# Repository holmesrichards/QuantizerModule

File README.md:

# QuantizerModule
Code and hardware for Kosmo/Eurorack quantizer module

This is a dual quantizer based on the [dac/ino](https://github.com/holmesrichards/dac_ino) board. As such it uses the dac\_ino library as well as the Quantizer library in this repository. 

Design is for Kosmo format module but the PCB and code would work equally well for a Eurorack version if the board were mounted perpendicular to the panel. It would just need a smaller front panel. Likewise with perpendicular mounting it could be a smaller single Kosmo quantizer.

## Front panel
On the front panel, for each quantizer section, are:

- CV1 and CV2 inputs
- Quantize gate input
- Trigger input
- CV output
- CV2 attenuator
- Quantize toggle switch
- Scale selection 12 position rotary switch
- Bank selection 6 position switch

## Use
The control voltage to be quantized is plugged into CV1. It should be in the range 0–5 volts, though voltages outside this range (within reason) shouldn't cause damage.

CV2 is an offset; it is added to the quantized CV1 to produce the output. It should also be in the range 0–5 volts. It can be attenuated with the knob. Normalled value is 5 volts before attenuation.

The Quantize switch can be used to disable quantization, in which case the output CV is just CV1 + CV2 (attenuated). If the Quantize switch is on and a gate source is plugged into the Quantize input, quantization is on only when the gate is on. If nothing is plugged in and the Quantize switch is on, quantization is on.

If nothing is plugged into the Trigger input, the input control voltages are sampled and the output control voltage is updated continually. If a trigger or gate source is plugged in, updating occurs only when a trigger or gate is present. In that case the module behaves like a quantizing (or not, if quantizing is off) sample and hold.

The rotary switches are used to select a bank of scales and a scale within that bank. There can be up to 12 scales stored in each of up to 6 banks, which makes 72 scales for those of you who've lost your calculator. ("Up to." Depending on the scales, 72 of them might exceed the Arduino's program memory capacity.) See [scales document](./docs/SCALES.md) for the scales built into the software as supplied. If you want other scales it's easy enough to change them. There's a mechanism to convert Scala format scale files, or definitions in terms of equal divisions of the octave or generators and periods into data for the Quantizer library. See [change scale instructions](./docs/CHANGESCALES.md).

## Current requirements
28 mA +12 V  
 4 mA -12 V

## Building
For build notes see [here](docs/BUILD.md).

## Software
A sketch and two libraries are required:

- [QuantSketch.ino](software/QuantSketch/QuantSketch.ino)
- [Quantizer library](software/Quantizer) (.cpp and .h files)
- [dac/ino library](https://github.com/holmesrichards/dac_ino/tree/master/software) (.cpp and .h files)

But the dac_ino library itself uses three libraries:

- Arduino, which is standard (built in to the IDE)
- SPI, which I think is also built in to the IDE
- DirectIO, from here: https://github.com/mmarchetti/DirectIO.git For this you apparently just need DirectIO.h, there is no .cpp file.

On my system (Linux, off-line Arduino IDE) the non standard libraries are in sub-folders, named Quantizer, dac_ino, and DirectIO, of the ~/Arduino/libraries folder. QuantSketch.ino can be anywhere though the IDE wants it to be inside a folder called QuantSketch. For details and other platforms and IDEs, consult Arduino documentation.

## Credits
The Quantizer library and the table building script are based on work by Brendon Cassidy, see https://github.com/bpcmusic/telex and https://github.com/bpcmusic/telex_scales .

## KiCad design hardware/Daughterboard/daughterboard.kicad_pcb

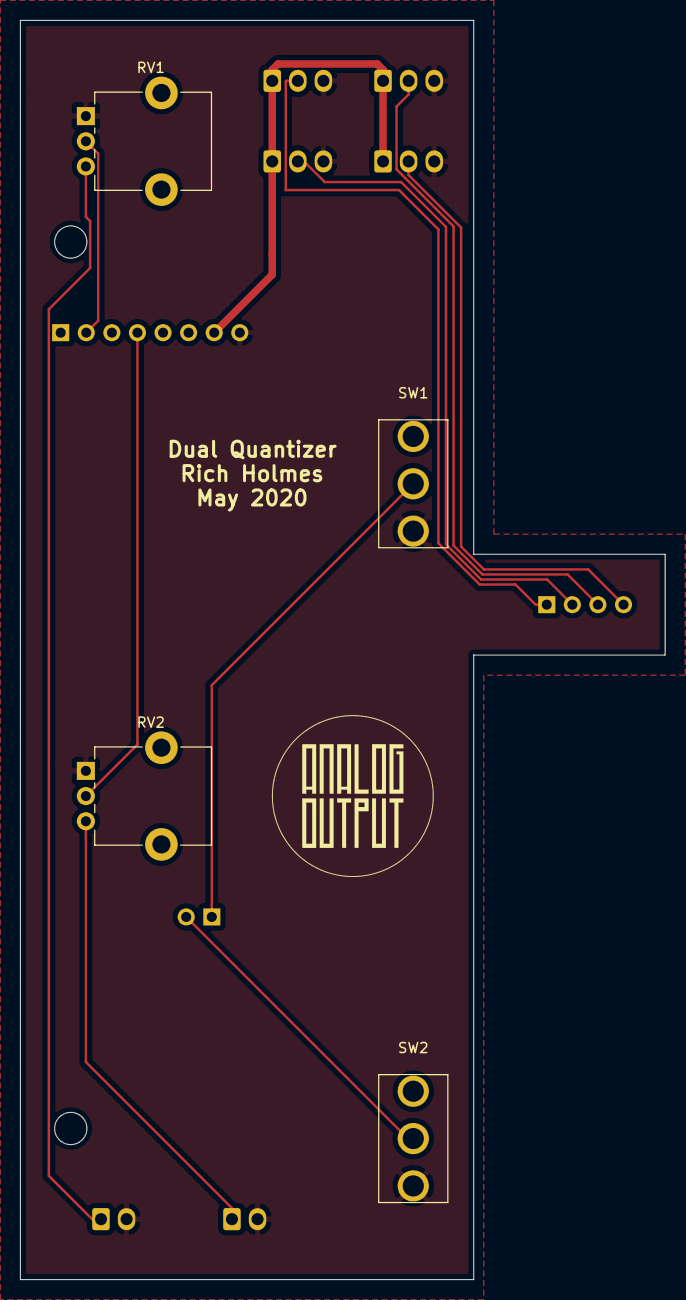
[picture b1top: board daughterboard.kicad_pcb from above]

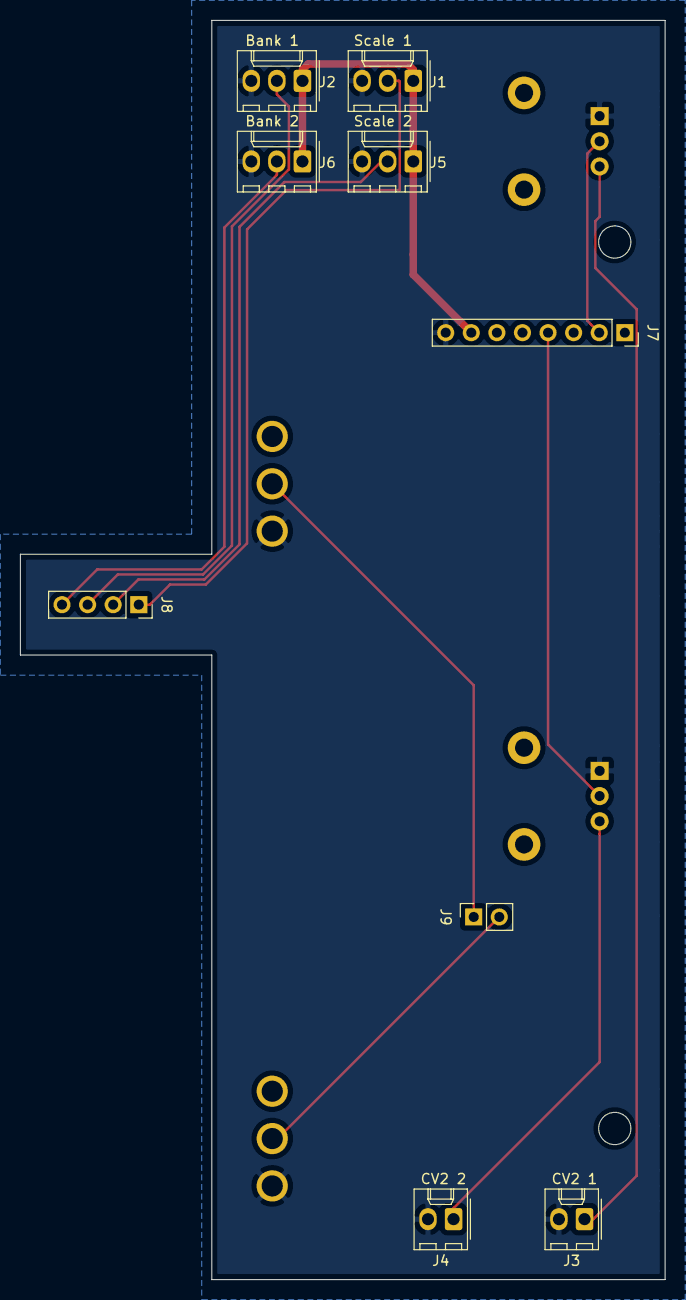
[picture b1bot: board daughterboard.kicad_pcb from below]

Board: 2 copper layers, 64.0 x 125.0 mm, 15 parts (9 on the bottom side), 12 nets.

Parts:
H3, H4: MountingHole; MountingHole_3.2mm_M3
J1: Conn_01x03 Scale_1; Molex_KK-254_AE-6410-03A_1x03_P2.54mm_Vertical
J2: Conn_01x03 Scale_2; Molex_KK-254_AE-6410-03A_1x03_P2.54mm_Vertical
J3: Conn_01x02 CV2_1; Molex_KK-254_AE-6410-02A_1x02_P2.54mm_Vertical
J4: Conn_01x02 CV2_2; Molex_KK-254_AE-6410-02A_1x02_P2.54mm_Vertical
J5: Conn_01x03 Bank_1; Molex_KK-254_AE-6410-03A_1x03_P2.54mm_Vertical
J6: Conn_01x03 Bank_2; Molex_KK-254_AE-6410-03A_1x03_P2.54mm_Vertical
J7: Conn_01x08; PinSocket_1x08_P2.54mm_Vertical
J8: Conn_01x04; PinSocket_1x04_P2.54mm_Vertical
J9: Conn_01x02; PinSocket_1x02_P2.54mm_Vertical
RV1, RV2: 10k; Potentiometer_Alpha_RD901F-40-00D_Single_Vertical_CircularH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
SW1: SW_SPST Quantize_1; SPDT-toggle-switch-1M-series
SW2: SW_SPST Quantize_2; SPDT-toggle-switch-1M-series

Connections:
GND: J1.3, J2.3, J3.2, J4.2, J5.3, J6.3, J7.8, RV1.1, RV2.1, SW1.1, SW2.1
unnamed: J1.2, J8.1
unnamed: J2.2, J8.3
unnamed: J3.1, RV1.3
unnamed: J4.1, RV2.3
unnamed: J5.2, J8.2
unnamed: J6.2, J8.4
unnamed: J7.2, RV1.2
unnamed: J7.4, RV2.2
unnamed: J9.1, SW1.2
unnamed: J9.2, SW2.2
VCC: J1.1, J2.1, J5.1, J6.1, J7.7

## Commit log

2020-04-13 Initial version
2020-04-13 Add mention of table_builder.py
2020-04-13 One word: dual
2020-04-13 More details of the planned module
2020-04-13 Add generator and period scales
2020-04-13 Ignore my stuff
2020-04-13 Panel tweaks
2020-04-13 Add code for trigger and gate
2020-04-14 Never mind about the svg files
2020-04-14 Incomplete revision of scales list
2020-04-14 Index more notes
2020-04-14 Specify generator-period scales and et scales in the main file
2020-04-14 Debugging and format change
2020-04-14 Reduction to 6 banks; near-full set of scales defined
2020-04-14 Panel revision for 6 banks
2020-04-23 No margin
2020-04-23 table_builder.py now handles organization into banks
2020-05-13 dac/ino name change; README tweak
2020-06-08 First PCB version, backlog of numerous changes including daughterboard
2020-06-08 Note on dac/ino version
2020-08-22 Lots of updates belatedly committed
2020-08-26 Reorganization and debugging
2020-08-26 table_builder revisions, common and esoteric scale sets
2020-08-26 Put triggers on Gate In A and B; debug table_builder, scales files; corrected scale info into Quantizer
2020-08-26 Use common scales
2020-08-26 Documentation
2020-08-26 Documentation more
2020-08-26 photo
2020-08-26 improve scales doc format
2020-08-26 improve change scales doc format
2020-08-26 Credits
2020-08-26 Back photo
2020-08-27 Turn off debug
2020-08-27 Comments
2020-08-27 Fix error in dim 7
2020-08-27 Duh, 4095 is 10 V not 5
2020-08-28 Build photos
2020-08-28 Typo in BUILD
2020-08-28 Get rid of old daughterboard stuff
2020-08-30 Software notes
2020-08-30 Software notes redux
2020-09-07 Fix link to panel components schematic.
2020-09-27 Update BUILD.md
    Correct "Gate" to "Trigger" and add resistor values
2020-09-27 Update namespace name
2020-12-07 Build doc clarifications
2021-01-17 Include lib table files
2021-01-24 Build notes improvements
2021-01-24 Renumber references
2021-02-02 Fix link error
2021-02-02 Renumber panel components
2021-02-02 Fix link
2021-03-13 Clarify resistors on jacks and toggles
